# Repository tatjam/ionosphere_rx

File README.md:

# Electronically tunable capacitor

This repo contains the hardware and firmware for a electronically tunable capacitor designed for RX loop antennas.

Here's how it looks (sorry for the dirty board, I was actively moving jumpers around as this photo was taken!)

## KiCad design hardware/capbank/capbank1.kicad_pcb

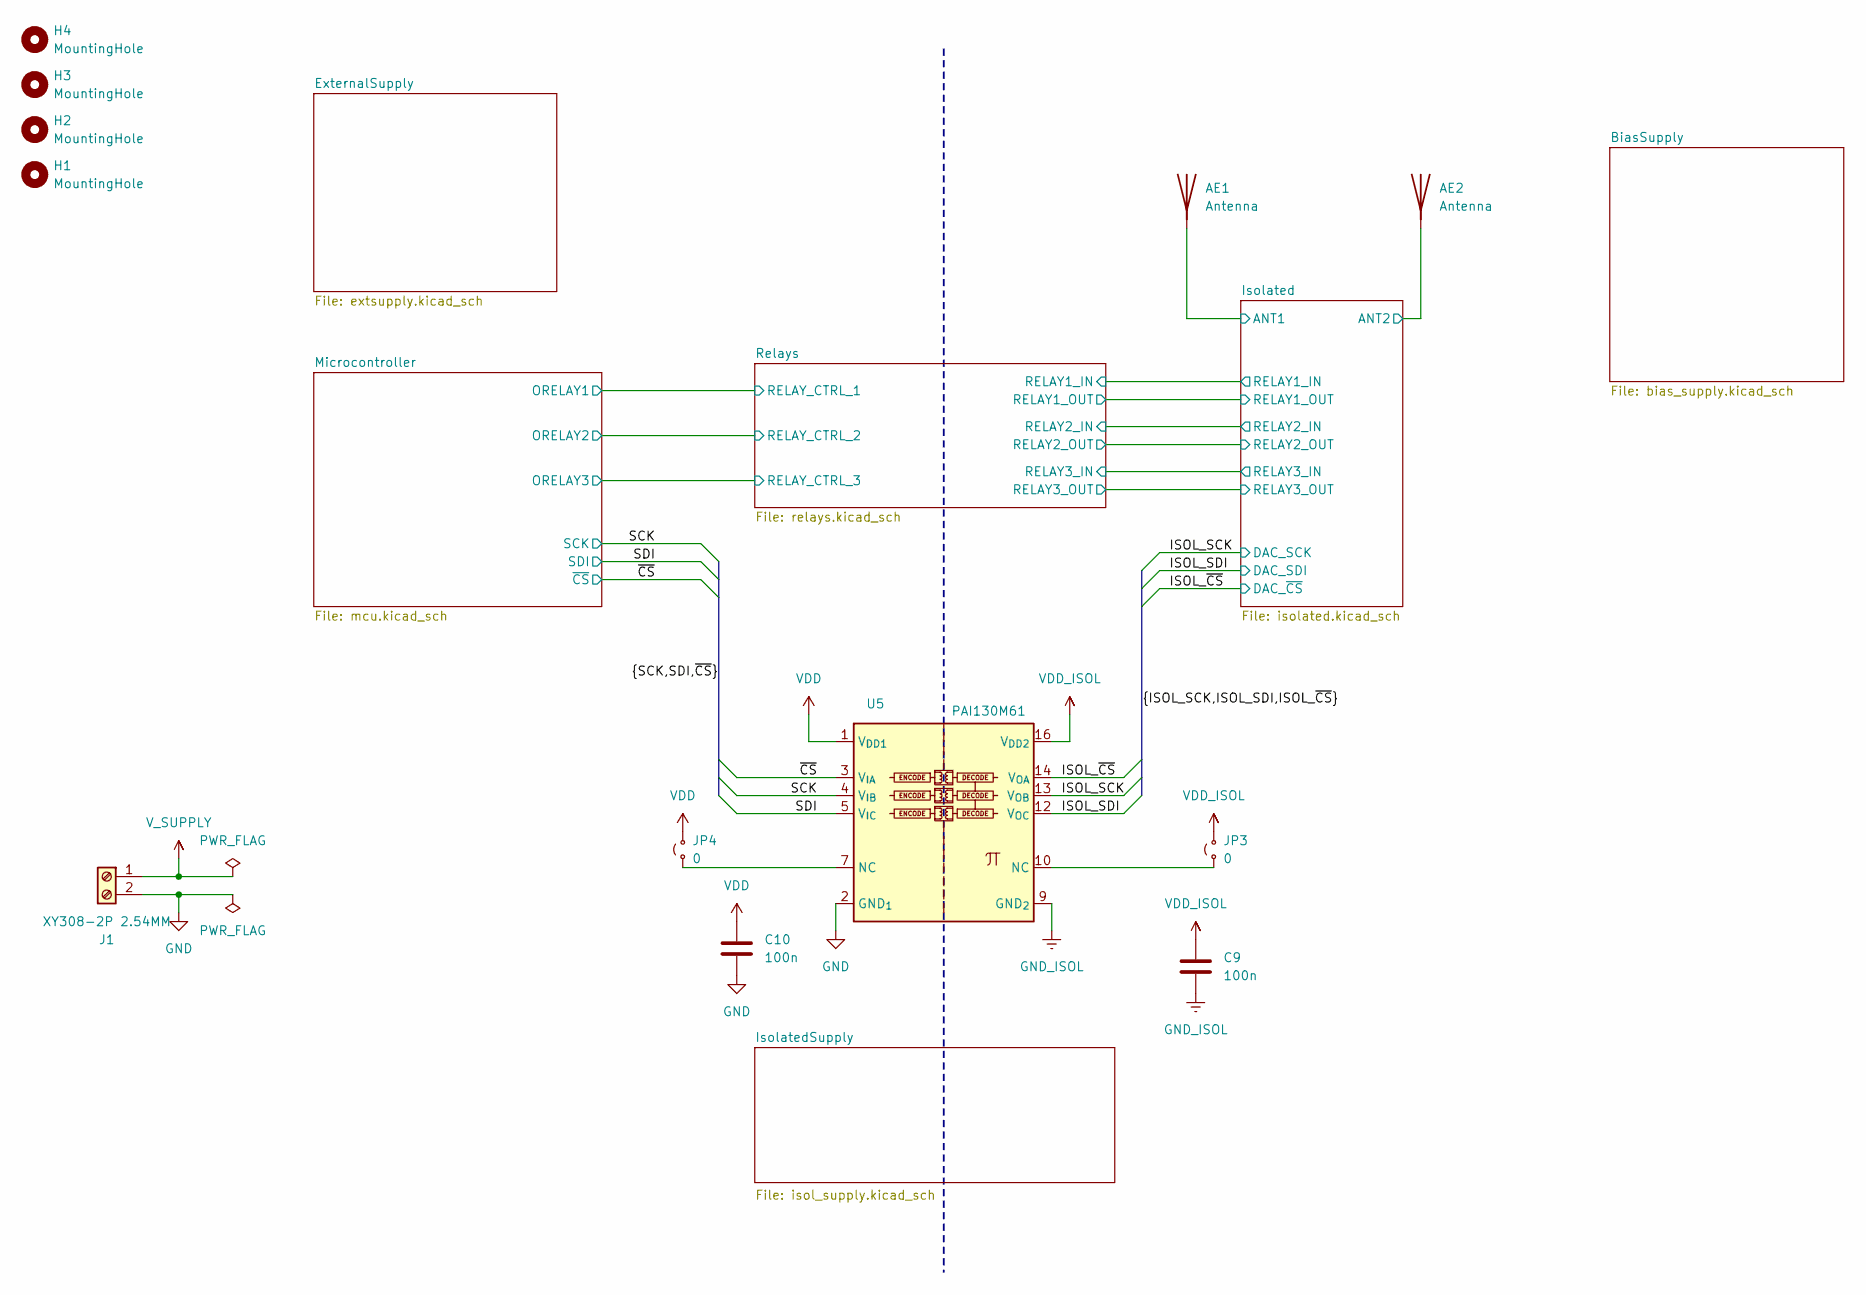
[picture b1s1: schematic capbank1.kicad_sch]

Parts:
AE1, AE2: Antenna; SolderWire-1.5sqmm_1x01_D1.7mm_OD3.9mm_Relief
C9, C10: 100n; C_0603_1608Metric
H1, H2, H3, H4: MountingHole; MountingHole_3.2mm_M3
J1: XY308-2P 2.54MM; TerminalBlock_Phoenix_MPT-0,5-2-2.54_1x02_P2.54mm_Horizontal
JP3, JP4: 0; R_0603_1608Metric
U5: PAI130M61; SOIC-16W_7.5x10.3mm_P1.27mm

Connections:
/ISOL_SCK: U5.13 (V_{OB}); also elsewhere on the board
/ISOL_SDI: U5.12 (V_{OC}); also elsewhere on the board
/ISOL_~CS: U5.14 (V_{OA}); also elsewhere on the board
/Isolated/ANT1: AE1.1 (A); also elsewhere on the board
/Isolated/ANT2: AE2.1 (A); also elsewhere on the board
/SCK: U5.4 (V_{IB}); also elsewhere on the board
/SDI: U5.5 (V_{IC}); also elsewhere on the board
/~CS: U5.3 (V_{IA}); also elsewhere on the board
GND: C10.2, J1.2, U5.2 (GND_{1}), U5.8 (GND_{1}); also elsewhere on the board
GND_ISOL: C9.2, U5.9 (GND_{2}), U5.15 (GND_{2}); also elsewhere on the board
unnamed: JP3.1 (A), U5.10 (NC)
unnamed: JP4.1 (A), U5.7 (NC)
VDD: C10.1, JP4.2 (B), U5.1 (V_{DD1}); also elsewhere on the board
VDD_ISOL: C9.1, JP3.2 (B), U5.16 (V_{DD2}); also elsewhere on the board
V_SUPPLY: J1.1; also elsewhere on the board

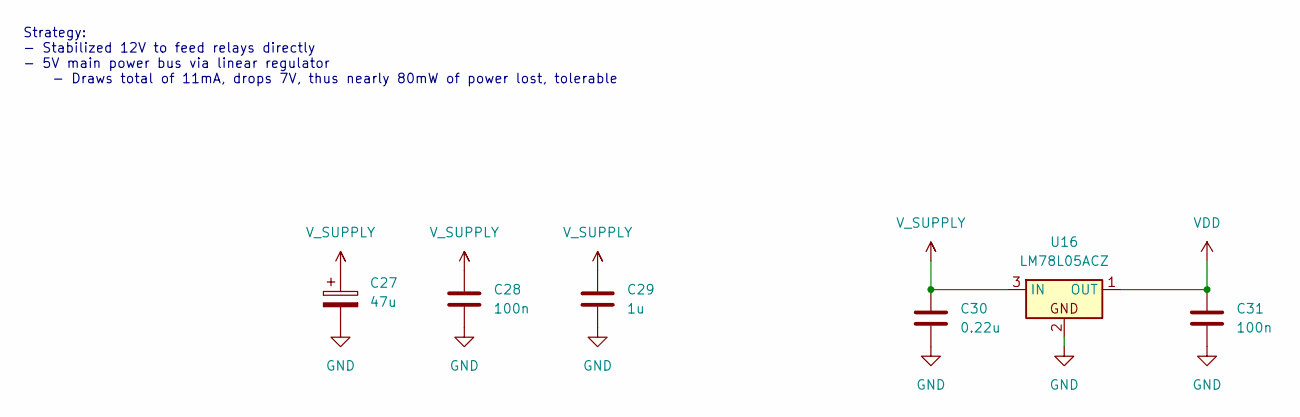
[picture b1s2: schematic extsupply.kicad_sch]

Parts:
C27: 47u; CP_Radial_D6.3mm_P2.50mm
C28, C31: 100n; C_0603_1608Metric
C29: 1u; C_0603_1608Metric
C30: 0.22u; C_0603_1608Metric
U16: LM78L05ACZ; TO-92_Inline_Wide

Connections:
GND: C27.2, C28.2, C29.2, C30.2, C31.2, U16.2; also elsewhere on the board
VDD: C31.1, U16.1 (OUT); also elsewhere on the board
V_SUPPLY: C27.1, C28.1, C29.1, C30.1, U16.3 (IN); also elsewhere on the board

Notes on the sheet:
Strategy: - Stabilized 12V to feed relays directly - 5V main power bus via linear regulator - Draws total of 11mA, drops 7V, thus nearly 80mW of power lost, tolerable

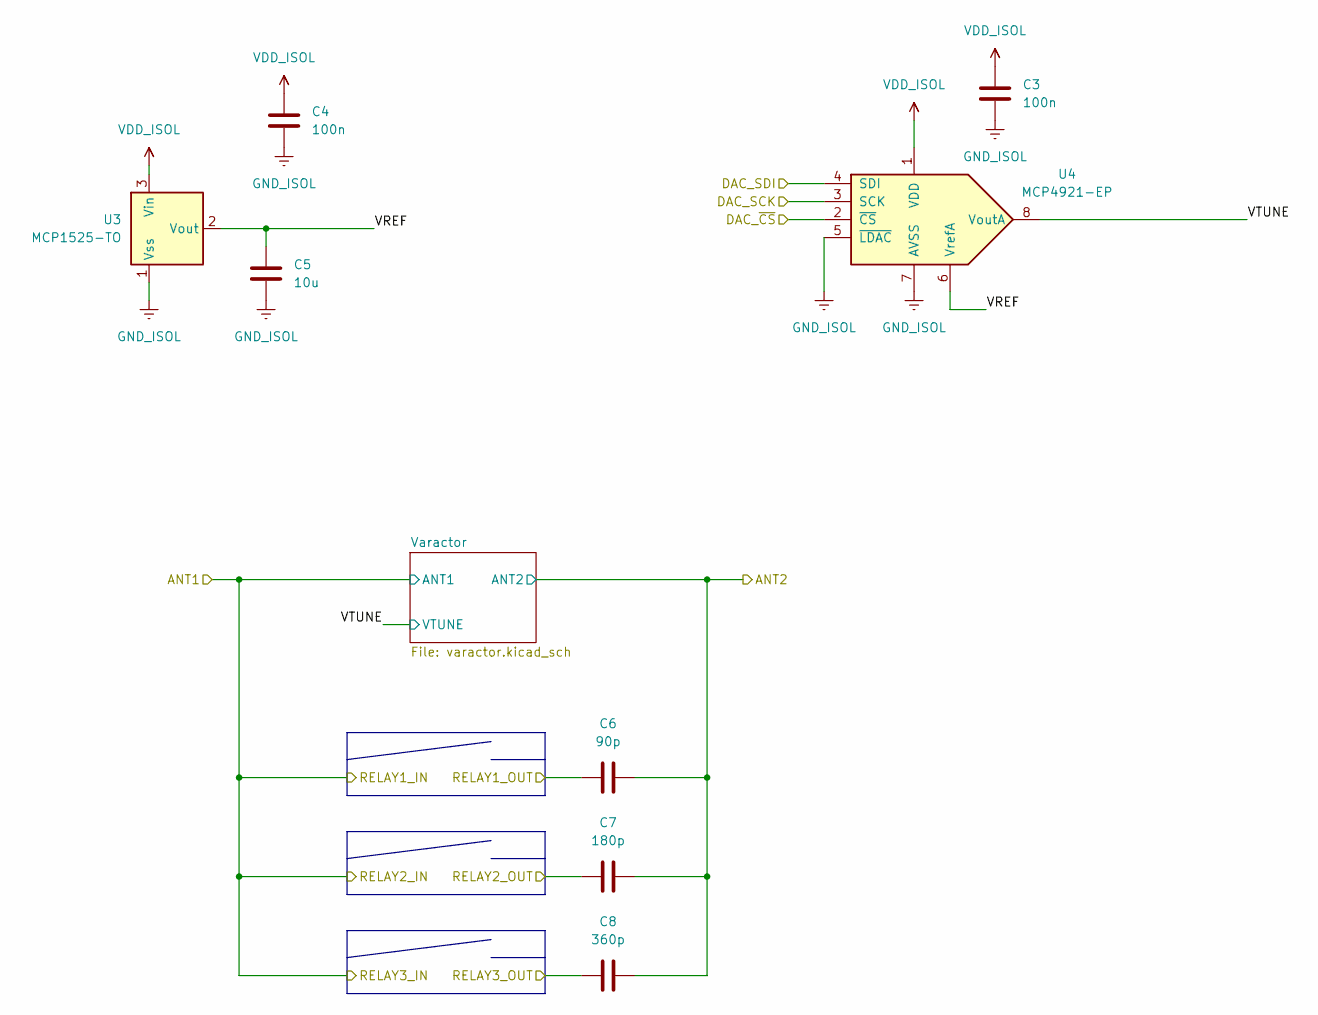
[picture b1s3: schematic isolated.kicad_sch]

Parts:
C3, C4: 100n; C_0603_1608Metric
C5: 10u; C_0603_1608Metric
C6: 90p; C_0603_1608Metric
C7: 180p; C_0603_1608Metric
C8: 360p; C_0603_1608Metric
U3: MCP1525-TO; TO-92_Inline
U4: MCP4921-EP; DIP-8_W7.62mm

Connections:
/ISOL_SCK: U4.3 (SCK); also elsewhere on the board
/ISOL_SDI: U4.4 (SDI); also elsewhere on the board
/ISOL_~CS: U4.2 (~CS); also elsewhere on the board
/Isolated/ANT2: C6.2, C7.2, C8.2; also elsewhere on the board
/Isolated/RELAY1_OUT: C6.1; also elsewhere on the board
/Isolated/RELAY2_OUT: C7.1; also elsewhere on the board
/Isolated/RELAY3_OUT: C8.1; also elsewhere on the board
/Isolated/VREF: C5.1, U3.2 (Vout), U4.6 (VrefA)
/Isolated/VTUNE: U4.8 (VoutA); also elsewhere on the board
GND_ISOL: C3.2, C4.2, C5.2, U3.1 (Vss), U4.5 (~LDAC), U4.7 (AVSS); also elsewhere on the board
VDD_ISOL: C3.1, C4.1, U3.3 (Vin), U4.1 (VDD); also elsewhere on the board

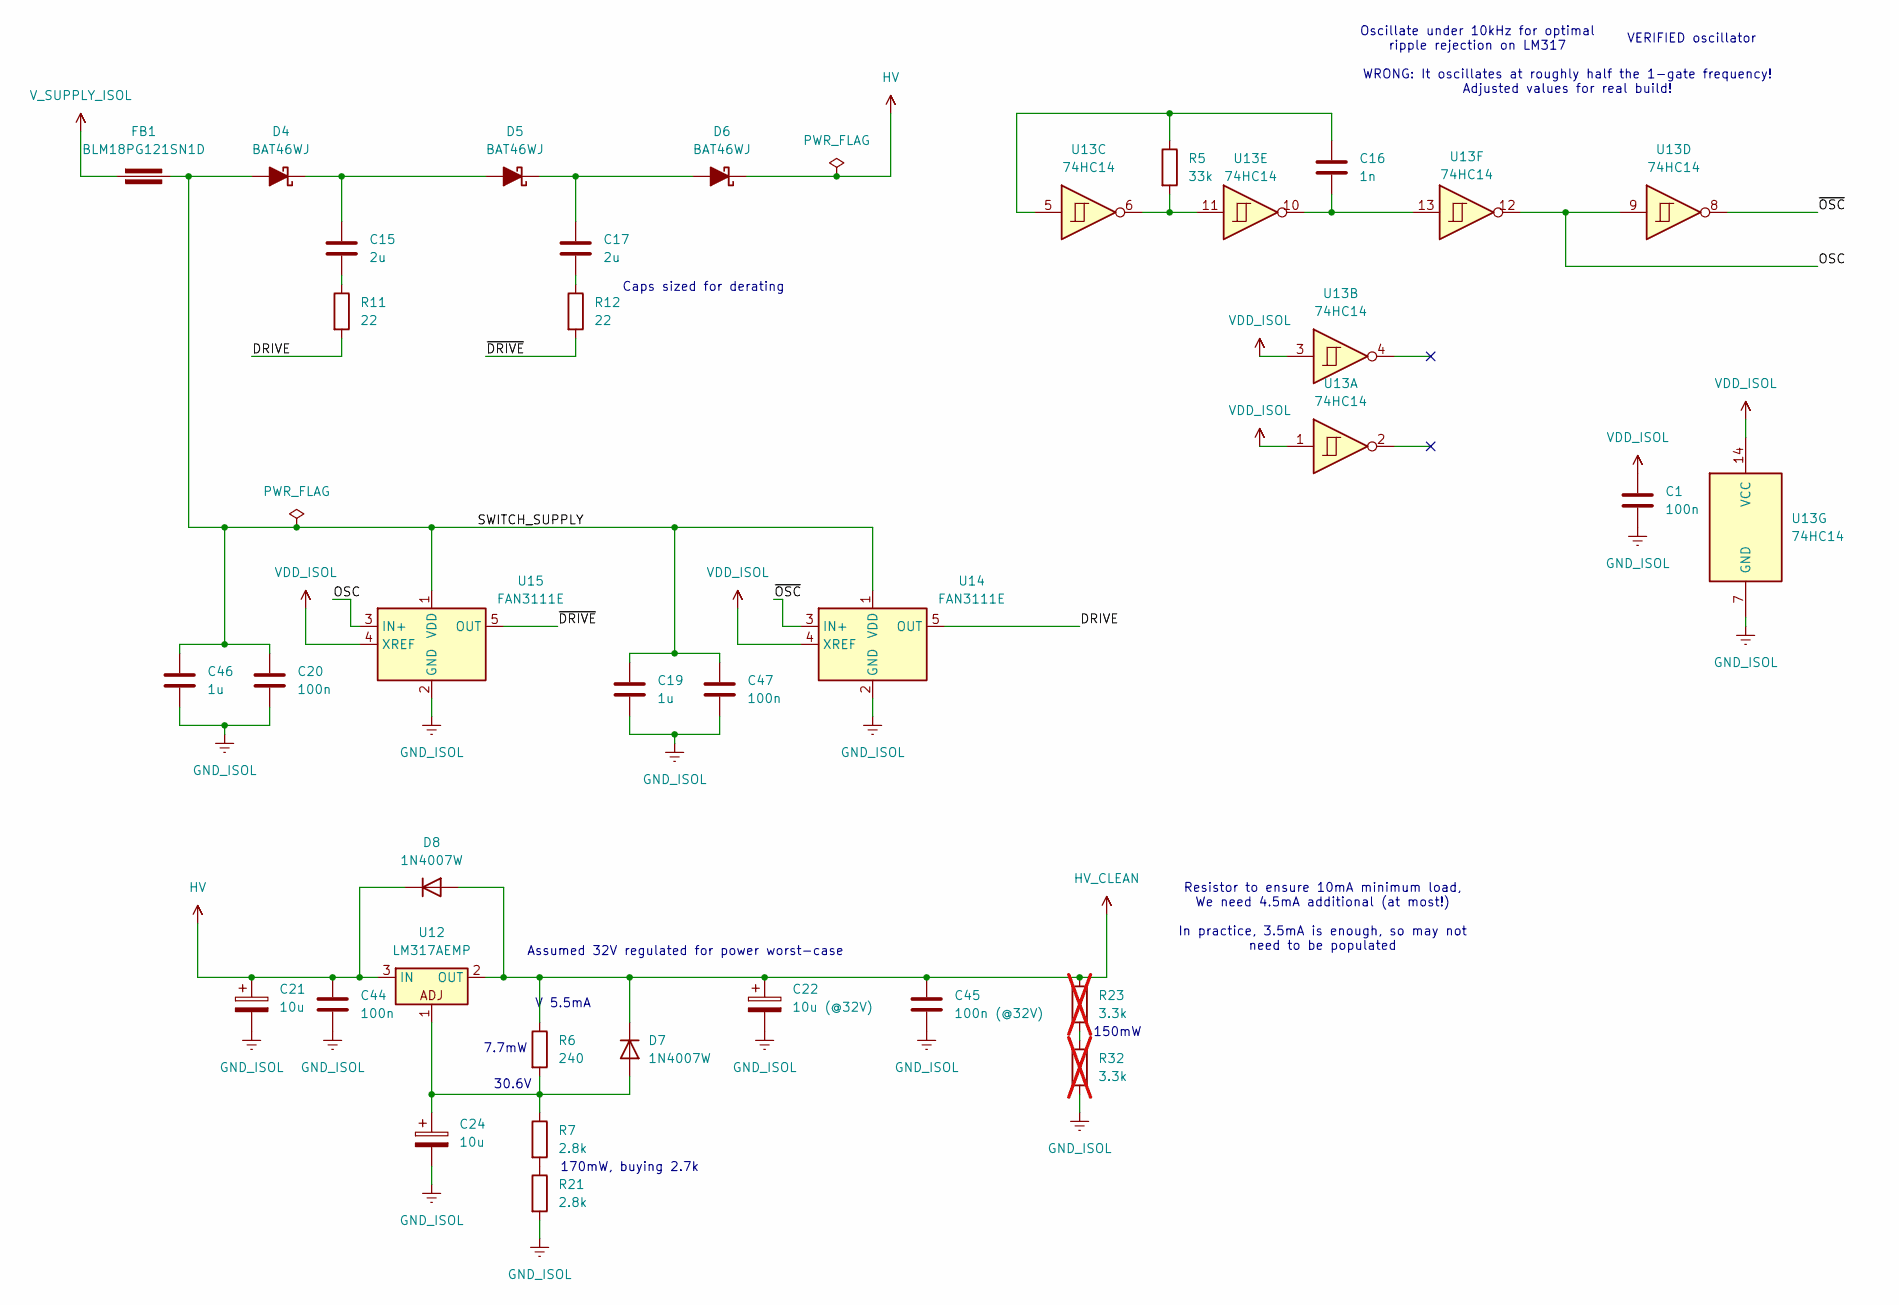
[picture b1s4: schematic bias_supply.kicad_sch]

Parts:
C1, C20, C44, C47: 100n; C_0603_1608Metric
C15, C17: 2u; C_0603_1608Metric
C16: 1n; C_0603_1608Metric
C19, C46: 1u; C_0603_1608Metric
C21, C24: 10u; CP_Radial_D5.0mm_P2.00mm
C22: 10u (@32V); CP_Radial_D5.0mm_P2.00mm
C45: 100n (@32V); C_0603_1608Metric
D4, D5, D6: BAT46WJ; D_SOD-323
D7, D8: 1N4007W; D_SOD-123
FB1: BLM18PG121SN1D; Ferrite_0603_1608Metric
R5: 33k; R_0603_1608Metric
R6: 240; R_0603_1608Metric
R7, R21: 2.8k; R_1206_3216Metric_Pad1.30x1.75mm_HandSolder
R11, R12: 22; R_0603_1608Metric
R23, R32: 3.3k; R_1206_3216Metric_Pad1.30x1.75mm_HandSolder; not fitted
U12: LM317AEMP; SOT-223-3_TabPin2
U13: 74HC14; SOIC-14_3.9x8.7mm_P1.27mm
U14, U15: FAN3111E; SOT-23-5

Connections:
/BiasSupply/DRIVE: R11.2, U14.5 (OUT)
/BiasSupply/OSC: U13.9, U13.12, U15.3 (IN+)
/BiasSupply/SWITCH_SUPPLY: C19.1, C20.1, C46.1, C47.1, D4.2 (A), FB1.2, U14.1 (VDD), U15.1 (VDD)
/BiasSupply/~DRIVE: R12.2, U15.5 (OUT)
/BiasSupply/~OSC: U13.8, U14.3 (IN+)
GND_ISOL: C1.2, C19.2, C20.2, C21.2, C22.2, C24.2, C44.2, C45.2, C46.2, C47.2, R21.2, R32.2, U13.7 (GND), U14.2 (GND), U15.2 (GND); also elsewhere on the board
HV: C21.1, C44.1, D6.1 (K), D8.1 (K), U12.3 (IN)
HV_CLEAN: C22.1, C45.1, D7.1 (K), D8.2 (A), R6.1, R23.1, U12.2 (OUT); also elsewhere on the board
unnamed: C15.2, R11.1
unnamed: C16.1, R5.1, U13.5
unnamed: C16.2, U13.10, U13.13
unnamed: C17.2, R12.1
unnamed: C15.1, D4.1 (K), D5.2 (A)
unnamed: C17.1, D5.1 (K), D6.2 (A)
unnamed: C24.1, D7.2 (A), R6.2, R7.1, U12.1
unnamed: R5.2, U13.6, U13.11
unnamed: R7.2, R21.1
unnamed: R23.2, R32.1
VDD_ISOL: C1.1, U13.1, U13.3, U13.14 (VCC), U14.4 (XREF), U15.4 (XREF); also elsewhere on the board
V_SUPPLY_ISOL: FB1.1; also elsewhere on the board

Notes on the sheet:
WRONG: It oscillates at roughly half the 1-gate frequency! Adjusted values for real build!
VERIFIED oscillator
30.6V
150mW
Oscillate under 10kHz for optimal ripple rejection on LM317
Assumed 32V regulated for power worst-case
7.7mW
Resistor to ensure 10mA minimum load, We need 4.5mA additional (at most!) In practice, 3.5mA is enough, so may not need to be populated
170mW, buying 2.7k
V 5.5mA
Caps sized for derating

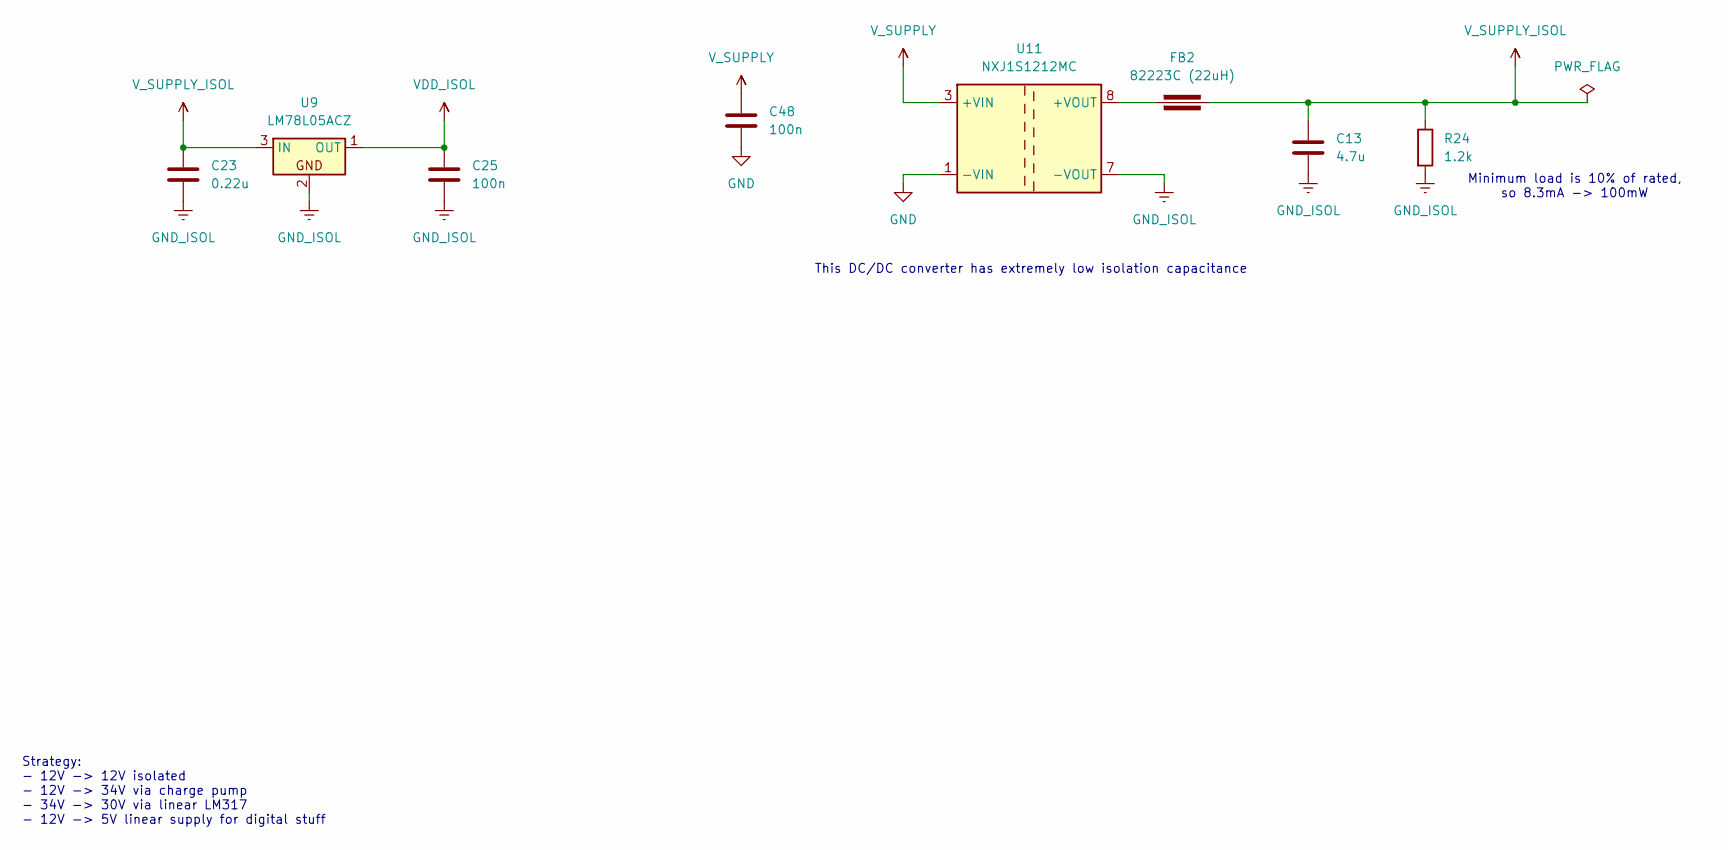
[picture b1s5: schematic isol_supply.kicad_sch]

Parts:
C13: 4.7u; C_1210_3225Metric_Pad1.33x2.70mm_HandSolder
C23: 0.22u; C_0603_1608Metric
C25, C48: 100n; C_0603_1608Metric
FB2: 82223C (22uH); 82223C
R24: 1.2k; R_1206_3216Metric_Pad1.30x1.75mm_HandSolder
U9: LM78L05ACZ; TO-92_Inline_Wide
U11: NXJ1S1212MC; NXJ1

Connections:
GND: C48.2, U11.1 (-VIN); also elsewhere on the board
GND_ISOL: C13.2, C23.2, C25.2, R24.2, U9.2, U11.7 (-VOUT); also elsewhere on the board
unnamed: FB2.1, U11.8 (+VOUT)
VDD_ISOL: C25.1, U9.1 (OUT); also elsewhere on the board
V_SUPPLY: C48.1, U11.3 (+VIN); also elsewhere on the board
V_SUPPLY_ISOL: C13.1, C23.1, FB2.2, R24.1, U9.3 (IN); also elsewhere on the board

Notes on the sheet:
Strategy: - 12V -> 12V isolated - 12V -> 34V via charge pump - 34V -> 30V via linear LM317 - 12V -> 5V linear supply for digital stuff
Minimum load is 10% of rated, so 8.3mA -> 100mW
This DC/DC converter has extremely low isolation capacitance

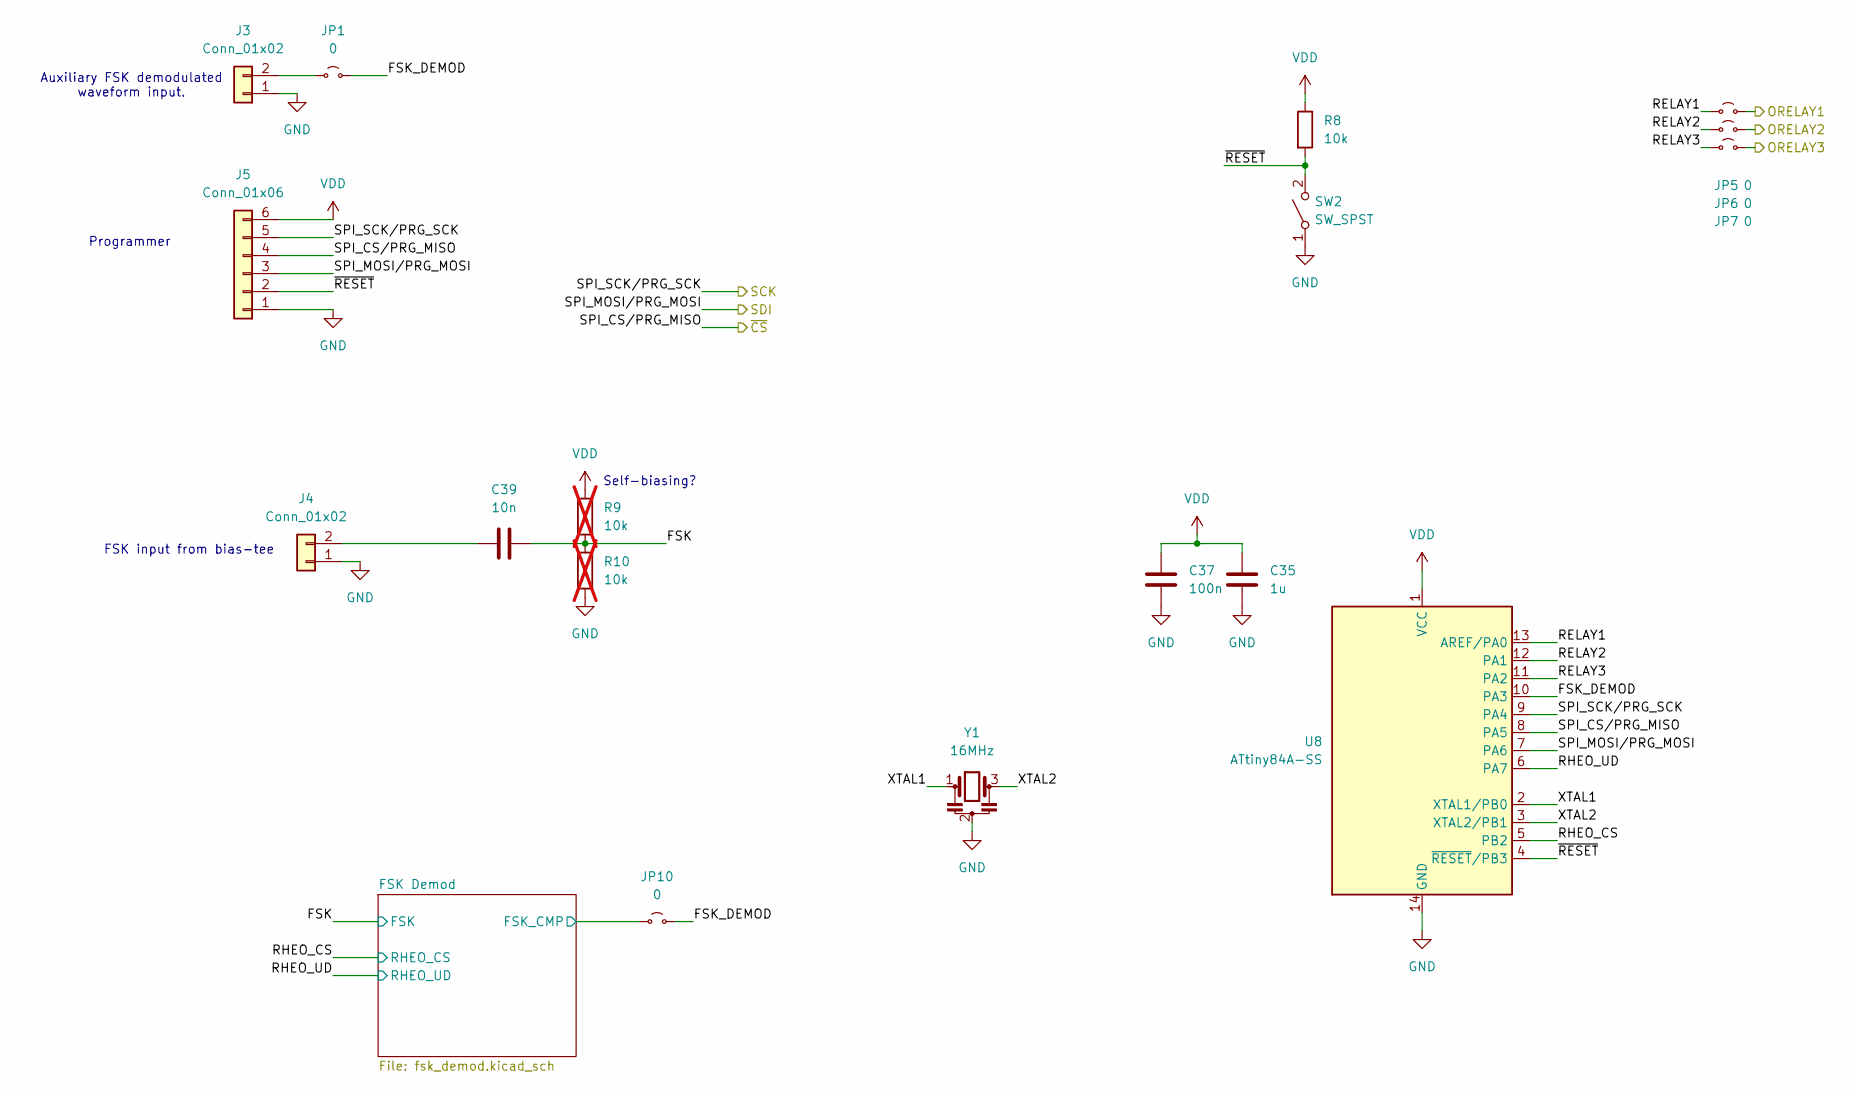
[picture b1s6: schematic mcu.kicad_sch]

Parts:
C35: 1u; C_0603_1608Metric
C37: 100n; C_0603_1608Metric
C39: 10n; C_0603_1608Metric
J3, J4: Conn_01x02; PinHeader_1x02_P2.54mm_Vertical
J5: Conn_01x06
JP1, JP5, JP6, JP7, JP10: 0; R_0603_1608Metric
R8: 10k; R_0603_1608Metric
R9, R10: 10k; R_0603_1608Metric; not fitted
SW2: SW_SPST; SW_SPST_CK_KXT3
U8: ATtiny84A-SS; SOIC-14_3.9x8.7mm_P1.27mm
Y1: 16MHz; Resonator_SMD_muRata_CSTxExxV-3Pin_3.0x1.1mm_BigPads

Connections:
/Microcontroller/FSK: C39.2, R9.2, R10.1; also elsewhere on the board
/Microcontroller/FSK Demod/FSK_CMP: JP10.1 (A); also elsewhere on the board
/Microcontroller/FSK_DEMOD: JP1.2 (B), JP10.2 (B), U8.10 (PA3)
/Microcontroller/ORELAY1: JP5.2 (B); also elsewhere on the board
/Microcontroller/ORELAY2: JP6.2 (B); also elsewhere on the board
/Microcontroller/ORELAY3: JP7.2 (B); also elsewhere on the board
/Microcontroller/RELAY1: JP5.1 (A), U8.13 (AREF/PA0)
/Microcontroller/RELAY2: JP6.1 (A), U8.12 (PA1)
/Microcontroller/RELAY3: JP7.1 (A), U8.11 (PA2)
/Microcontroller/RHEO_CS: U8.5 (PB2); also elsewhere on the board
/Microcontroller/RHEO_UD: U8.6 (PA7); also elsewhere on the board
/Microcontroller/XTAL1: U8.2 (XTAL1/PB0), Y1.1
/Microcontroller/XTAL2: U8.3 (XTAL2/PB1), Y1.3
/Microcontroller/~RESET: J5.2, R8.2, SW2.2 (B), U8.4 (~RESET/PB3)
/SCK: J5.5, U8.9 (PA4); also elsewhere on the board
/SDI: J5.3, U8.7 (PA6); also elsewhere on the board
/~CS: J5.4, U8.8 (PA5); also elsewhere on the board
GND: C35.2, C37.2, J3.1, J4.1, J5.1, R10.2, SW2.1 (A), U8.14 (GND), Y1.2; also elsewhere on the board
unnamed: J3.2, JP1.1 (A)
unnamed: C39.1, J4.2
VDD: C35.1, C37.1, J5.6, R8.1, R9.1, U8.1 (VCC); also elsewhere on the board

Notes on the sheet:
Programmer
Auxiliary FSK demodulated waveform input.
Self-biasing?
FSK input from bias-tee

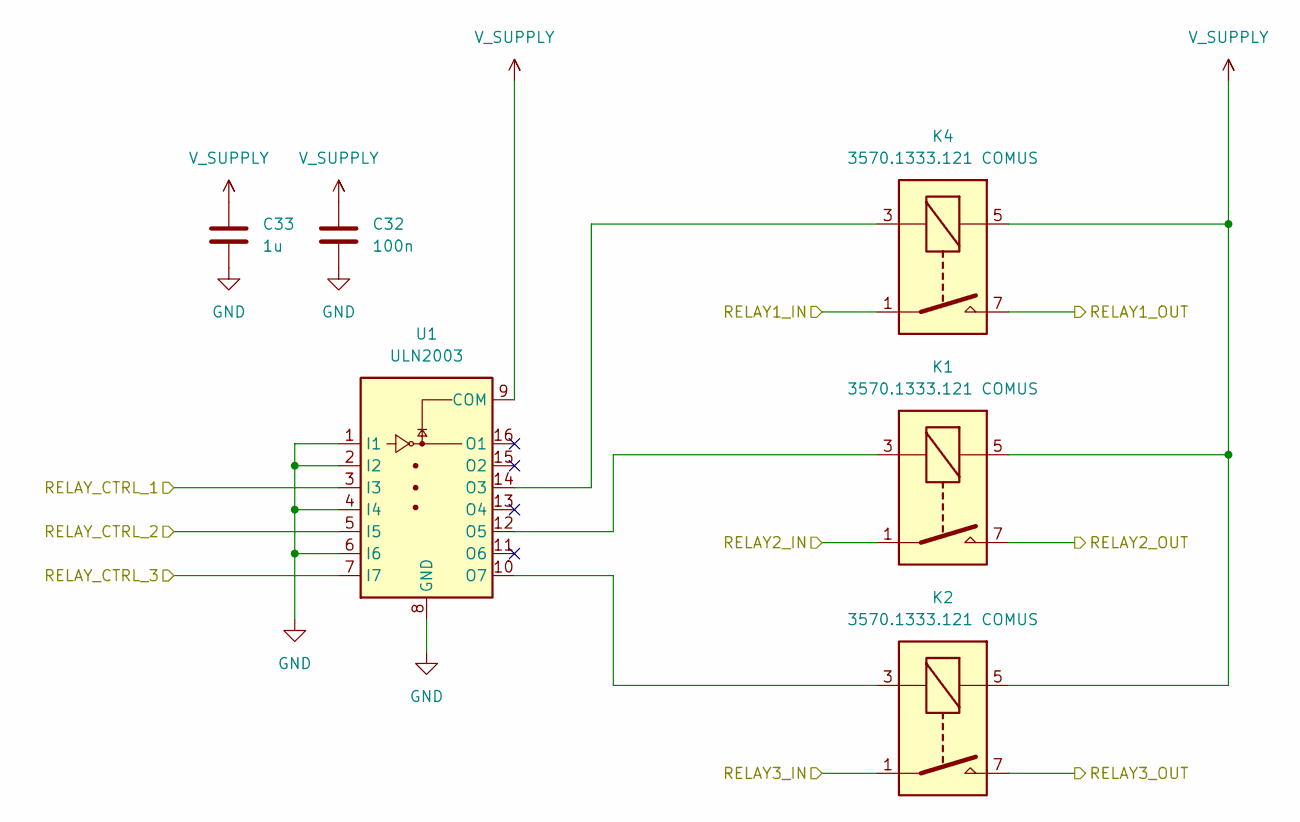
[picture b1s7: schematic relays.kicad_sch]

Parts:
C32: 100n; C_0603_1608Metric
C33: 1u; C_0603_1608Metric
K1, K2, K4: 3570.1333.121 COMUS; Relay_SPST_StandexMeder_SIL_Form1A
U1: ULN2003; SOIC-16_3.9x9.9mm_P1.27mm

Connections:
/Isolated/ANT1: K1.1, K2.1, K4.1; also elsewhere on the board
/Isolated/RELAY1_OUT: K4.7; also elsewhere on the board
/Isolated/RELAY2_OUT: K1.7; also elsewhere on the board
/Isolated/RELAY3_OUT: K2.7; also elsewhere on the board
/Microcontroller/ORELAY1: U1.3 (I3); also elsewhere on the board
/Microcontroller/ORELAY2: U1.5 (I5); also elsewhere on the board
/Microcontroller/ORELAY3: U1.7 (I7); also elsewhere on the board
GND: C32.2, C33.2, U1.1 (I1), U1.2 (I2), U1.4 (I4), U1.6 (I6), U1.8 (GND); also elsewhere on the board
unnamed: K4.3, U1.14 (O3)
unnamed: K1.3, U1.12 (O5)
unnamed: K2.3, U1.10 (O7)
V_SUPPLY: C32.1, C33.1, K1.5, K2.5, K4.5, U1.9 (COM); also elsewhere on the board

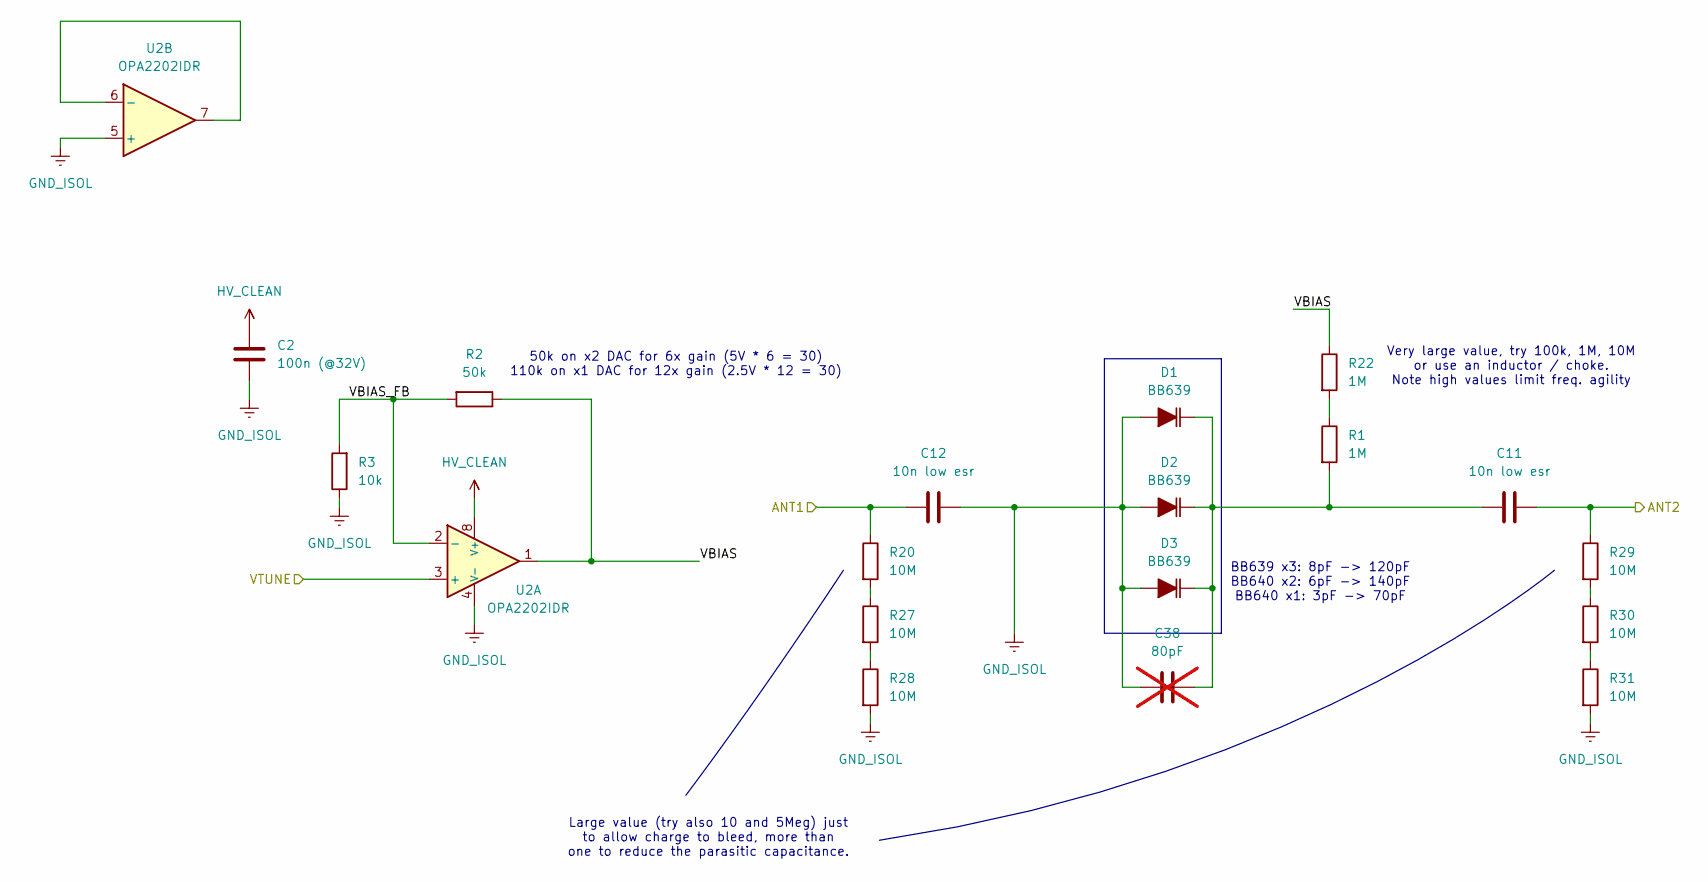
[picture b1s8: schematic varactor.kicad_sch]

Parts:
C2: 100n (@32V); C_0603_1608Metric
C11, C12: 10n low esr; C_1206_3216Metric
C38: 80pF; C_0603_1608Metric; not fitted
D1, D2, D3: BB639; D_SOD-323
R1, R22: 1M; R_0603_1608Metric
R2: 50k; R_0603_1608Metric
R3: 10k; R_0603_1608Metric
R20, R27, R28, R29, R30, R31: 10M; R_0603_1608Metric
U2: OPA2202IDR; SOIC-8_3.9x4.9mm_P1.27mm

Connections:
/Isolated/ANT1: C12.1, R20.1; also elsewhere on the board
/Isolated/ANT2: C11.2, R29.1; also elsewhere on the board
/Isolated/VTUNE: U2.3 (+); also elsewhere on the board
/Isolated/Varactor/VBIAS: R2.1, R22.1, U2.1
/Isolated/Varactor/VBIAS_FB: R2.2, R3.2, U2.2 (-)
GND_ISOL: C2.2, C12.2, C38.1, D1.2 (A), D2.2 (A), D3.2 (A), R3.1, R28.2, R31.2, U2.4 (V-), U2.5 (+); also elsewhere on the board
HV_CLEAN: C2.1, U2.8 (V+); also elsewhere on the board
unnamed: C11.1, C38.2, D1.1 (K), D2.1 (K), D3.1 (K), R1.2
unnamed: R1.1, R22.2
unnamed: R20.2, R27.1
unnamed: R27.2, R28.1
unnamed: R29.2, R30.1
unnamed: R30.2, R31.1
unnamed: U2.6 (-), U2.7

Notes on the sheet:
Large value (try also 10 and 5Meg) just to allow charge to bleed, more than one to reduce the parasitic capacitance.
50k on x2 DAC for 6x gain (5V * 6 = 30) 110k on x1 DAC for 12x gain (2.5V * 12 = 30)
BB639 x3: 8pF -> 120pF BB640 x2: 6pF -> 140pF BB640 x1: 3pF -> 70pF
Very large value, try 100k, 1M, 10M or use an inductor / choke. Note high values limit freq. agility

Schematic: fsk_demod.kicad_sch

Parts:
C14, C34, C40: 1n; C_0603_1608Metric
C18, C26, C41, C42, C43: 100n; C_0603_1608Metric
C36: 2n; C_0603_1608Metric
JP2, JP8, JP11, JP13, JP15: 0; R_0603_1608Metric
JP9, JP12, JP14, JP16: 0; R_0603_1608Metric; not fitted
R4, R16, R17, R25: 10k; R_0603_1608Metric
R13: 220k; R_0603_1608Metric
R14: 47k; R_0603_1608Metric
R15: 470; R_0603_1608Metric
R18, R19: 1.7k; R_0603_1608Metric
R26: 200k; R_0603_1608Metric
R33: 2.7k; R_0603_1608Metric
R34: 50k; R_0603_1608Metric; not fitted
U6: MCP6021T-E-OT; SOT-23-5
U7: 74HC4046AD; SOIC-16_3.9x9.9mm_P1.27mm
U10: TS861IL; SOT-23-5
U17: MCP4012-503ECH; SOT-23-6

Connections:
/Microcontroller/FSK: U7.14 (SigIn); also elsewhere on the board
/Microcontroller/FSK Demod/FSK_CMP: R26.1, U10.1; also elsewhere on the board
/Microcontroller/FSK Demod/FSK_DEMOD: JP2.2 (B), JP9.1 (A), JP11.1 (A), R17.1
/Microcontroller/FSK Demod/FSK_FILT: JP9.2 (B), JP13.2 (B), U10.4 (-)
/Microcontroller/FSK Demod/PC: JP14.2 (B), JP15.2 (B), JP16.2 (B), R15.1
/Microcontroller/FSK Demod/VCO_IN: C34.1, R15.2, R16.1, U7.9 (VCOin)
/Microcontroller/RHEO_CS: U17.4 (~CS); also elsewhere on the board
/Microcontroller/RHEO_UD: U17.3 (U/~D); also elsewhere on the board
GND: C14.2, C18.2, C26.2, C34.2, C41.2, C42.2, C43.2, JP12.1 (A), R4.2, R13.2, R14.2, R17.2, R33.1, U6.2 (V-), U7.8 (VSS), U10.2 (V-), U17.2 (VSS); also elsewhere on the board
unnamed: C36.1, R18.2, R19.1
unnamed: C41.1, R16.2
unnamed: JP2.1 (A), U7.10 (SFout)
unnamed: JP8.1 (A), U17.6 (A)
unnamed: JP11.2 (B), JP12.2 (B), R18.1
unnamed: C36.2, JP13.1 (A), U6.1, U6.4 (-)
unnamed: JP14.1 (A), U7.15 (ZOUT)
unnamed: JP15.1 (A), U7.13 (PC2)
unnamed: JP16.1 (A), U7.2 (PC1)
unnamed: C14.1, R19.2, U6.3 (+)
unnamed: C40.1, U7.6 (C1)
unnamed: C40.2, U7.7 (C2)
unnamed: U7.3 (RefIn), U7.4 (FOUT)
unnamed: R4.1, U7.5 (Inh)
unnamed: R13.1, U7.11 (R1)
unnamed: R14.1, U7.12 (R2)
unnamed: R25.2, R26.2, U10.3 (+)
unnamed: R25.1, R33.2, R34.1, U17.5 (W)
VDD: C18.1, C26.1, C42.1, C43.1, JP8.2 (B), R34.2, U6.5 (V+), U7.16 (VDD), U10.5 (V+), U17.1 (VDD); also elsewhere on the board

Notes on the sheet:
Cheaper: TLV9061xDBV
I[output positive] = (VCC - x * VCC) / (R26 + R_series) I[output negative] = x * VCC / (R26 + R_series)
Up to first order, for R26 >> R25 and R_[MCP] ~= R25: V+[output positive] = VCC * x + VCC * R25 / R26 V+[output negative] = VCC * x - VCC * R25 / R26 V+[output positive] > V+[output_negative] (If FSK_FILT < V+, output is positive, once FSK_FILT crosses V+, output jumps to negative, and as expected 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
Or CD74HC4046AM
For cd74hc4046a (dataset names): Tested working values that give f(0.8V) = 160kHz f(4.0V) = 315kHz R2 = 47k C1 = 1nF R2/R1 = 5 R1 = 220k (R1C1 = 220us) (R2C1 = 47us)
For 74HC_HCT4046A (dataset names): (Untested values) fl = 100kHz R1C1 = 4e-5 (40us) foff = 90kHz R2 = 150kOhm C1 = 700pF R1 = 57kOhm (R2C1 = 105us)
Thevenin equivalent R_series = x (1-x) * 10k + R25 V = x * VCC

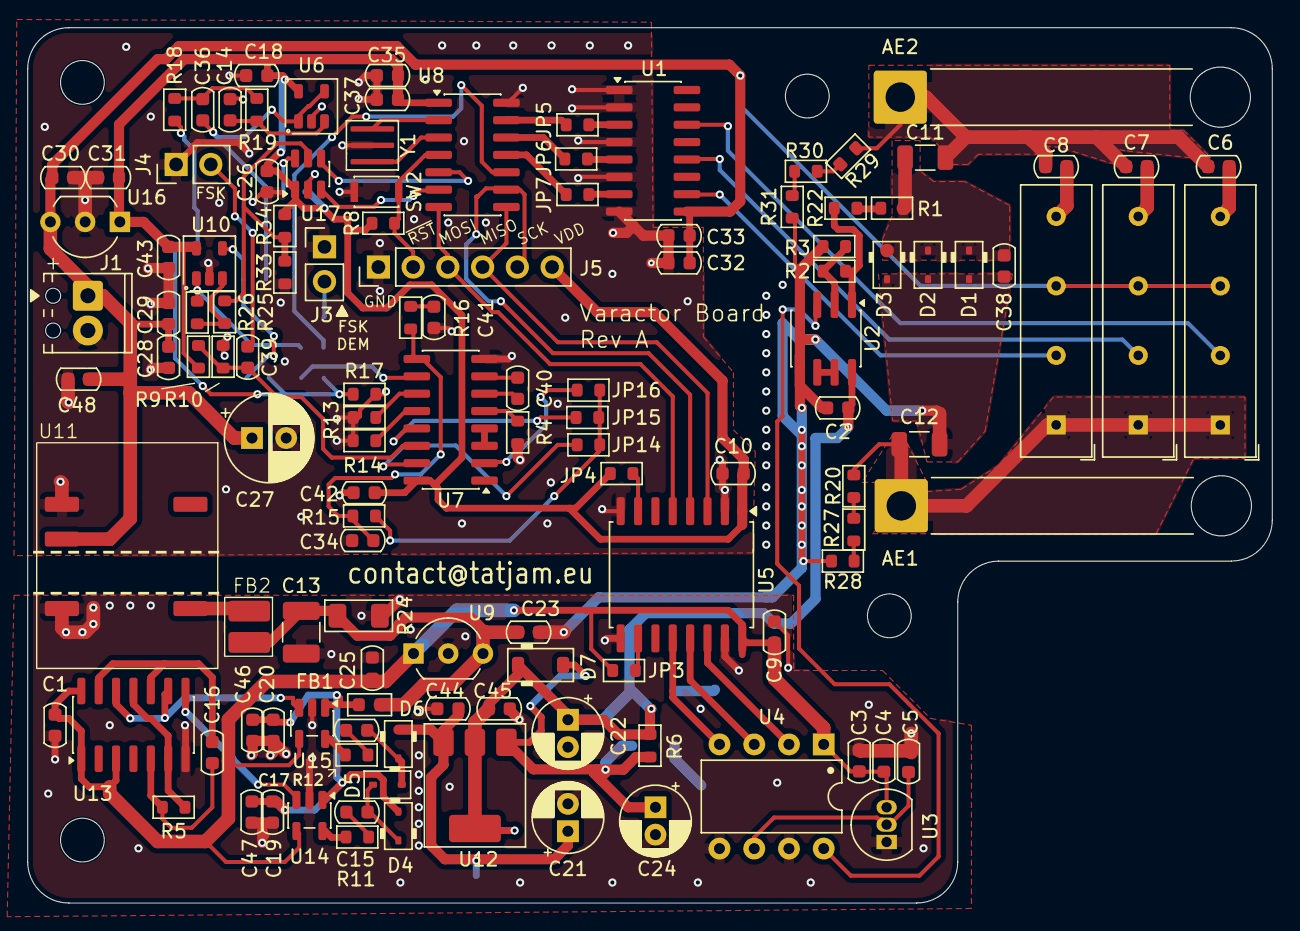
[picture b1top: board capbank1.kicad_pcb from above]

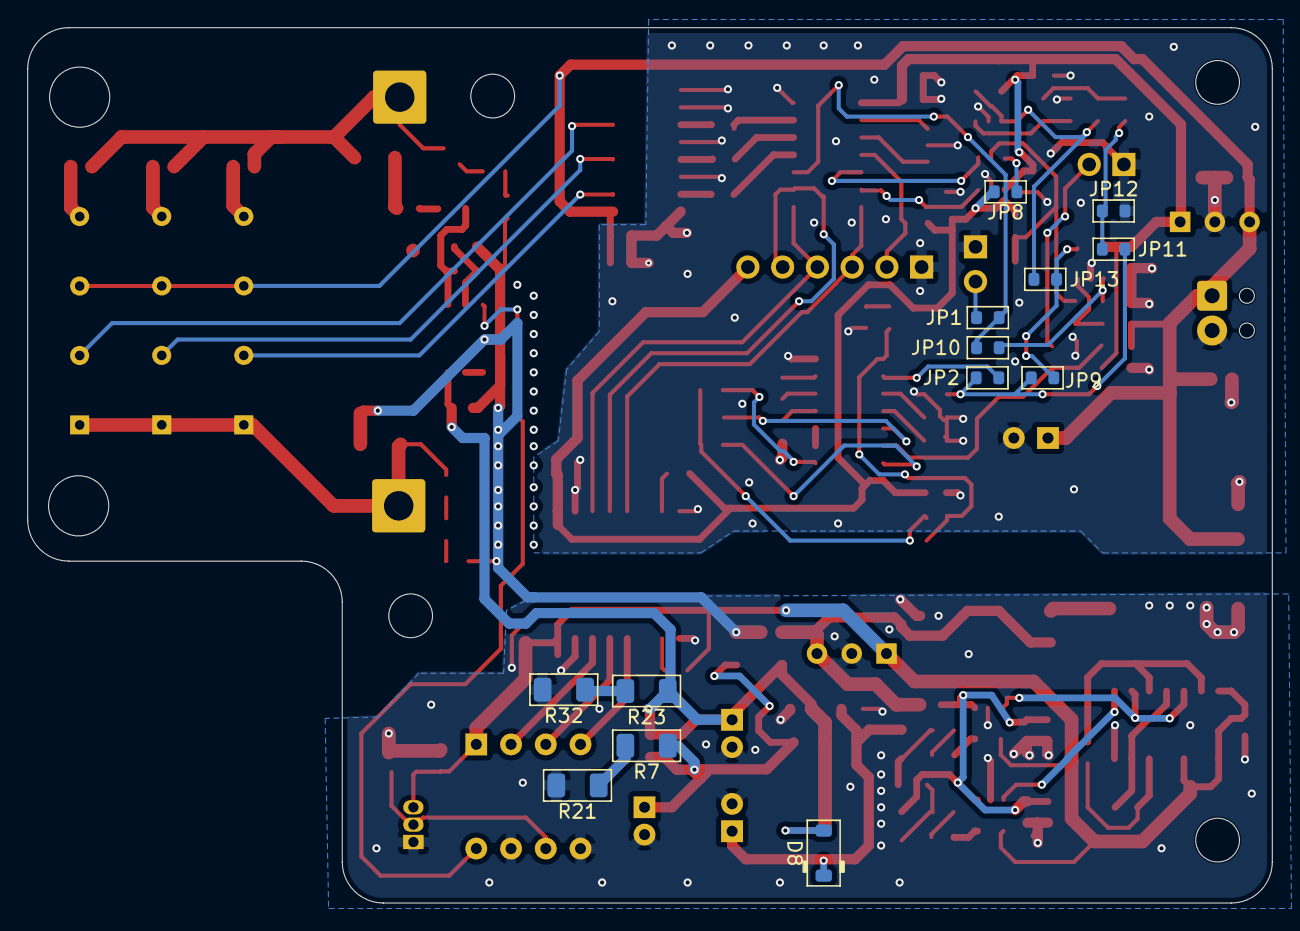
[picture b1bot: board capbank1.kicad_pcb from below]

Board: 2 copper layers, 91.0 x 64.0 mm, 140 parts (13 on the bottom side), 89 nets.

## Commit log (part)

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2026-04-13 Get started
2026-04-13 Add hardware and journal
2026-04-13 Add LICENSE
2026-04-13 Placed LICENSE on wrong folder
2026-04-13 Move stuff
2026-04-14 Blinky!
2026-04-17 Initial SPI DAC
2026-04-17 Small fixes and added "debug" LED back
2026-04-17 Make clock timing a bit more deterministic, not strictly needed but looks better on scope
    Also disable x2 output as it causes great loss in precision, correct in
    amplifier to drive the Varactor!
2026-04-18 Initial full firmware implementation
2026-04-19 KiCad changes
2026-04-19 Tuning experiments
2026-04-19 Experiments completed
2026-05-02 Get started with tests
2026-05-02 Small fixes revealed by tests
2026-05-03 Fixes revealed by tests
2026-05-25 Progress, layout nearly completed, build oscillator on breadboard
